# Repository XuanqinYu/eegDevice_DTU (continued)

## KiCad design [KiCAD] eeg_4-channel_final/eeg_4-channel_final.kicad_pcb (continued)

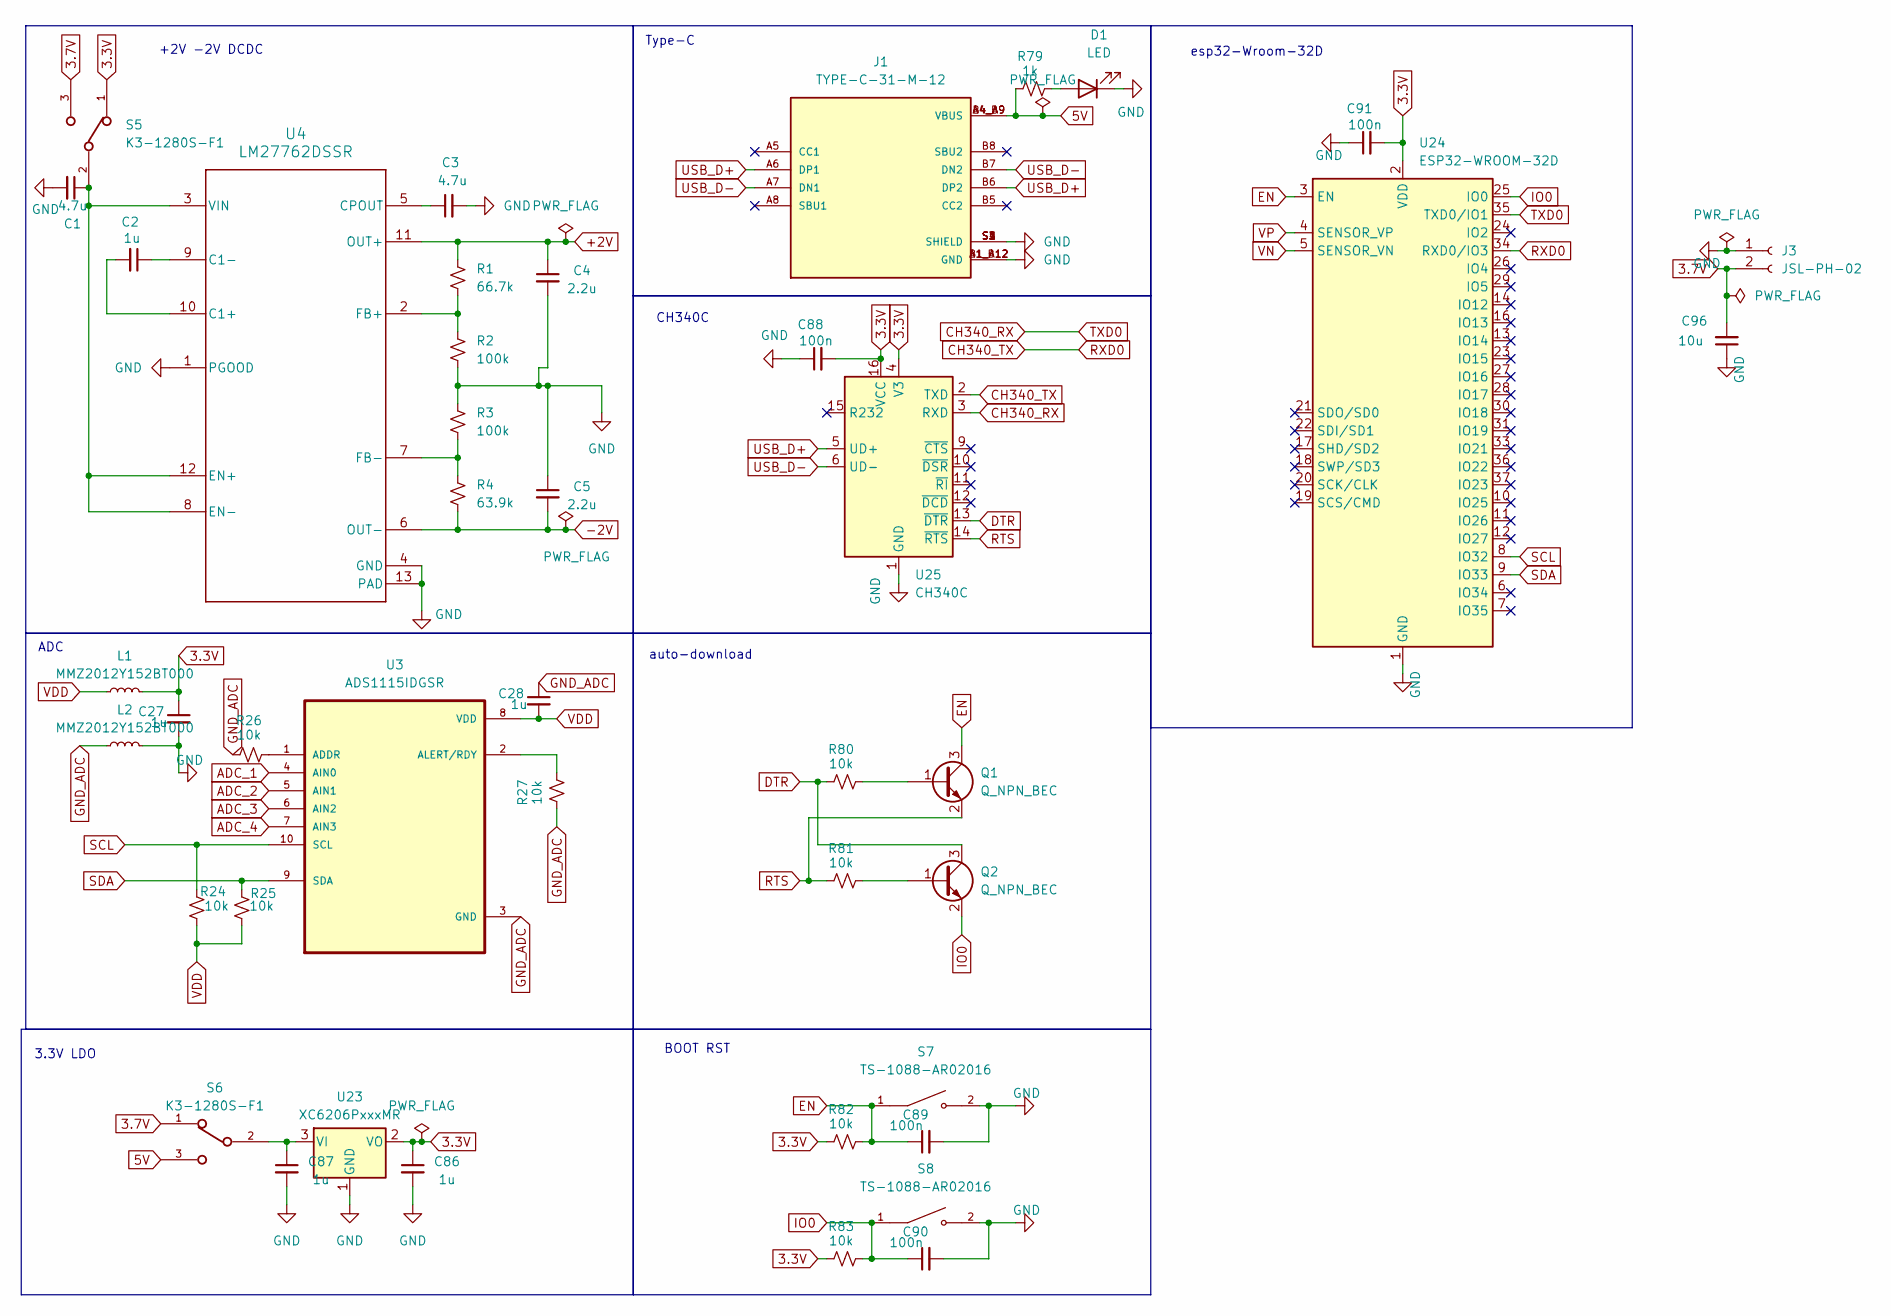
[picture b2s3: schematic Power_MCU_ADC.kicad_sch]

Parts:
C1, C3: 4.7u; C_0805_2012Metric
C2, C27, C28, C86, C87: 1u; C_0805_2012Metric
C4, C5: 2.2u; C_0603_1608Metric
C88, C89, C90, C91: 100n; C_0805_2012Metric
C96: 10u; C_0805_2012Metric
D1: LED; LED_0805_2012Metric
J1: TYPE-C-31-M-12; HRO_TYPE-C-31-M-12; PARTREV 2020.12.08
J3: JSL-PH-02; JST_PH_B2B-PH-K_1x02_P2.00mm_Vertical
L1, L2: MMZ2012Y152BT000; L_0805_2012Metric
Q1, Q2: Q_NPN_BEC; SOT-23
R1: 66.7k; R_0805_2012Metric
R2, R3: 100k; R_0603_1608Metric
R4: 63.9k; R_0805_2012Metric
R24, R25, R26, R27, R80, R81, R82, R83: 10k; R_0805_2012Metric
R79: 1k; R_0805_2012Metric
S5, S6: K3-1280S-F1; SW_JS102011SAQN
S7, S8: TS-1088-AR02016; SW_TS-1088-AR02016; PARTREV N/A
U3: ADS1115IDGSR; SOP50P490X110-10N
U4: LM27762DSSR; DSS0012B
U23: XC6206PxxxMR; SOT-23-3
U24: ESP32-WROOM-32D
U25: CH340C; SOIC-16_3.9x9.9mm_P1.27mm

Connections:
3.3V: C27.1, C86.1, C88.2, C91.2, L1.2, R82.1, R83.1, S5.1, U23.2 (VO), U24.2 (VDD), U25.4 (V3), U25.16 (VCC); also elsewhere on the board
3.7V: C96.2, J3.2, S5.3, S6.1
5V: J1.A4_B9 (VBUS), J1.B4_A9 (VBUS), R79.1, S6.3
+2V: C4.1, R1.2, U4.11 (OUT+); also elsewhere on the board
-2V: C5.2, R4.1, U4.6 (OUT-); also elsewhere on the board
ADC_1: U3.4 (AIN0); also elsewhere on the board
ADC_2: U3.5 (AIN1); also elsewhere on the board
ADC_3: U3.6 (AIN2); also elsewhere on the board
ADC_4: U3.7 (AIN3); also elsewhere on the board
CH340_RX: U24.35 (TXD0/IO1), U25.3 (RXD)
CH340_TX: U24.34 (RXD0/IO3), U25.2 (TXD)
DTR: Q2.3 (C), R80.1, U25.13 (~DTR)
EN: C89.1, Q1.3 (C), R82.2, S7.1, U24.3 (EN)
GND: C1.2, C3.2, C4.2, C5.1, C27.2, C86.2, C87.2, C88.1, C89.2, C90.2, C91.1, C96.1, D1.1 (K), J1.A1_B12 (GND), J1.B1_A12 (GND), J1.S1 (SHIELD), J1.S2 (SHIELD), J1.S3 (SHIELD), J1.S4 (SHIELD), J3.1, L2.2, R2.1, R3.2, S7.2, S8.2, U4.1 (PGOOD), U4.4 (GND), U4.13 (PAD), U23.1 (GND), U24.1 (GND), U24.15 (GND), U24.38 (GND), U24.39 (GND), U25.1 (GND); also elsewhere on the board
GND_ADC: C28.1, L2.1, R26.2, R27.2, U3.3 (GND)
IO0: C90.1, Q2.2 (E), R83.2, S8.1, U24.25 (IO0)
unnamed: D1.2 (A), R79.2
unnamed: Q1.1 (B), R80.2
unnamed: Q2.1 (B), R81.2
unnamed: R26.1, U3.1 (ADDR)
unnamed: R27.1, U3.2 (ALERT/RDY)
unnamed: C2.2, U4.10 (C1+)
unnamed: C2.1, U4.9 (C1-)
unnamed: C3.1, U4.5 (CPOUT)
unnamed: C1.1, S5.2, U4.3 (VIN), U4.8 (EN-), U4.12 (EN+)
unnamed: R1.1, R2.2, U4.2 (FB+)
unnamed: R3.1, R4.2, U4.7 (FB-)
unnamed: C87.1, S6.2, U23.3 (VI)
RTS: Q1.2 (E), R81.1, U25.14 (~RTS)
SCL: R24.2, U3.10 (SCL), U24.8 (IO32); also elsewhere on the board
SDA: R25.2, U3.9 (SDA), U24.9 (IO33); also elsewhere on the board
USB_D+: J1.A6 (DP1), J1.B6 (DP2), U25.5 (UD+)
USB_D-: J1.A7 (DN1), J1.B7 (DN2), U25.6 (UD-)
VDD: C28.2, L1.1, R24.1, R25.1, U3.8 (VDD)
VN: U24.5 (SENSOR_VN)
VP: U24.4 (SENSOR_VP)

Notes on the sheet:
ADC
BOOT RST
CH340C
3.3V LDO
auto-download
+2V -2V DCDC
Type-C
esp32-Wroom-32D

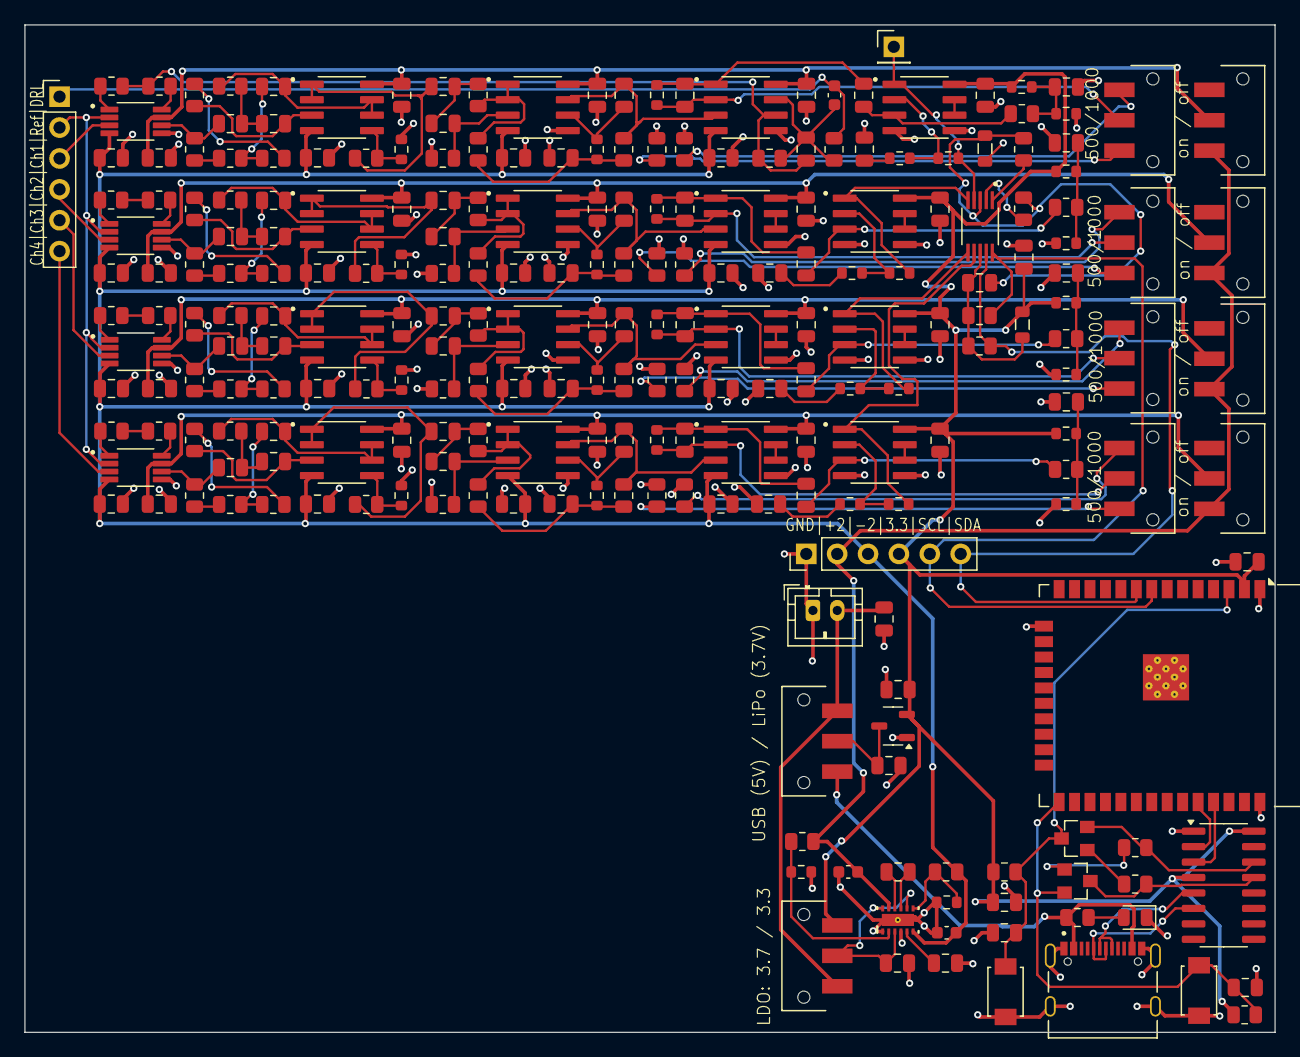
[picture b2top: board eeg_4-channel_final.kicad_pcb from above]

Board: 2 copper layers, 102.8 x 82.8 mm, 246 parts (0 on the bottom side), 152 nets.

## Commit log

2025-03-30 Create a
2025-03-30 工程文件
2025-04-14 editted at 2025/4/14
